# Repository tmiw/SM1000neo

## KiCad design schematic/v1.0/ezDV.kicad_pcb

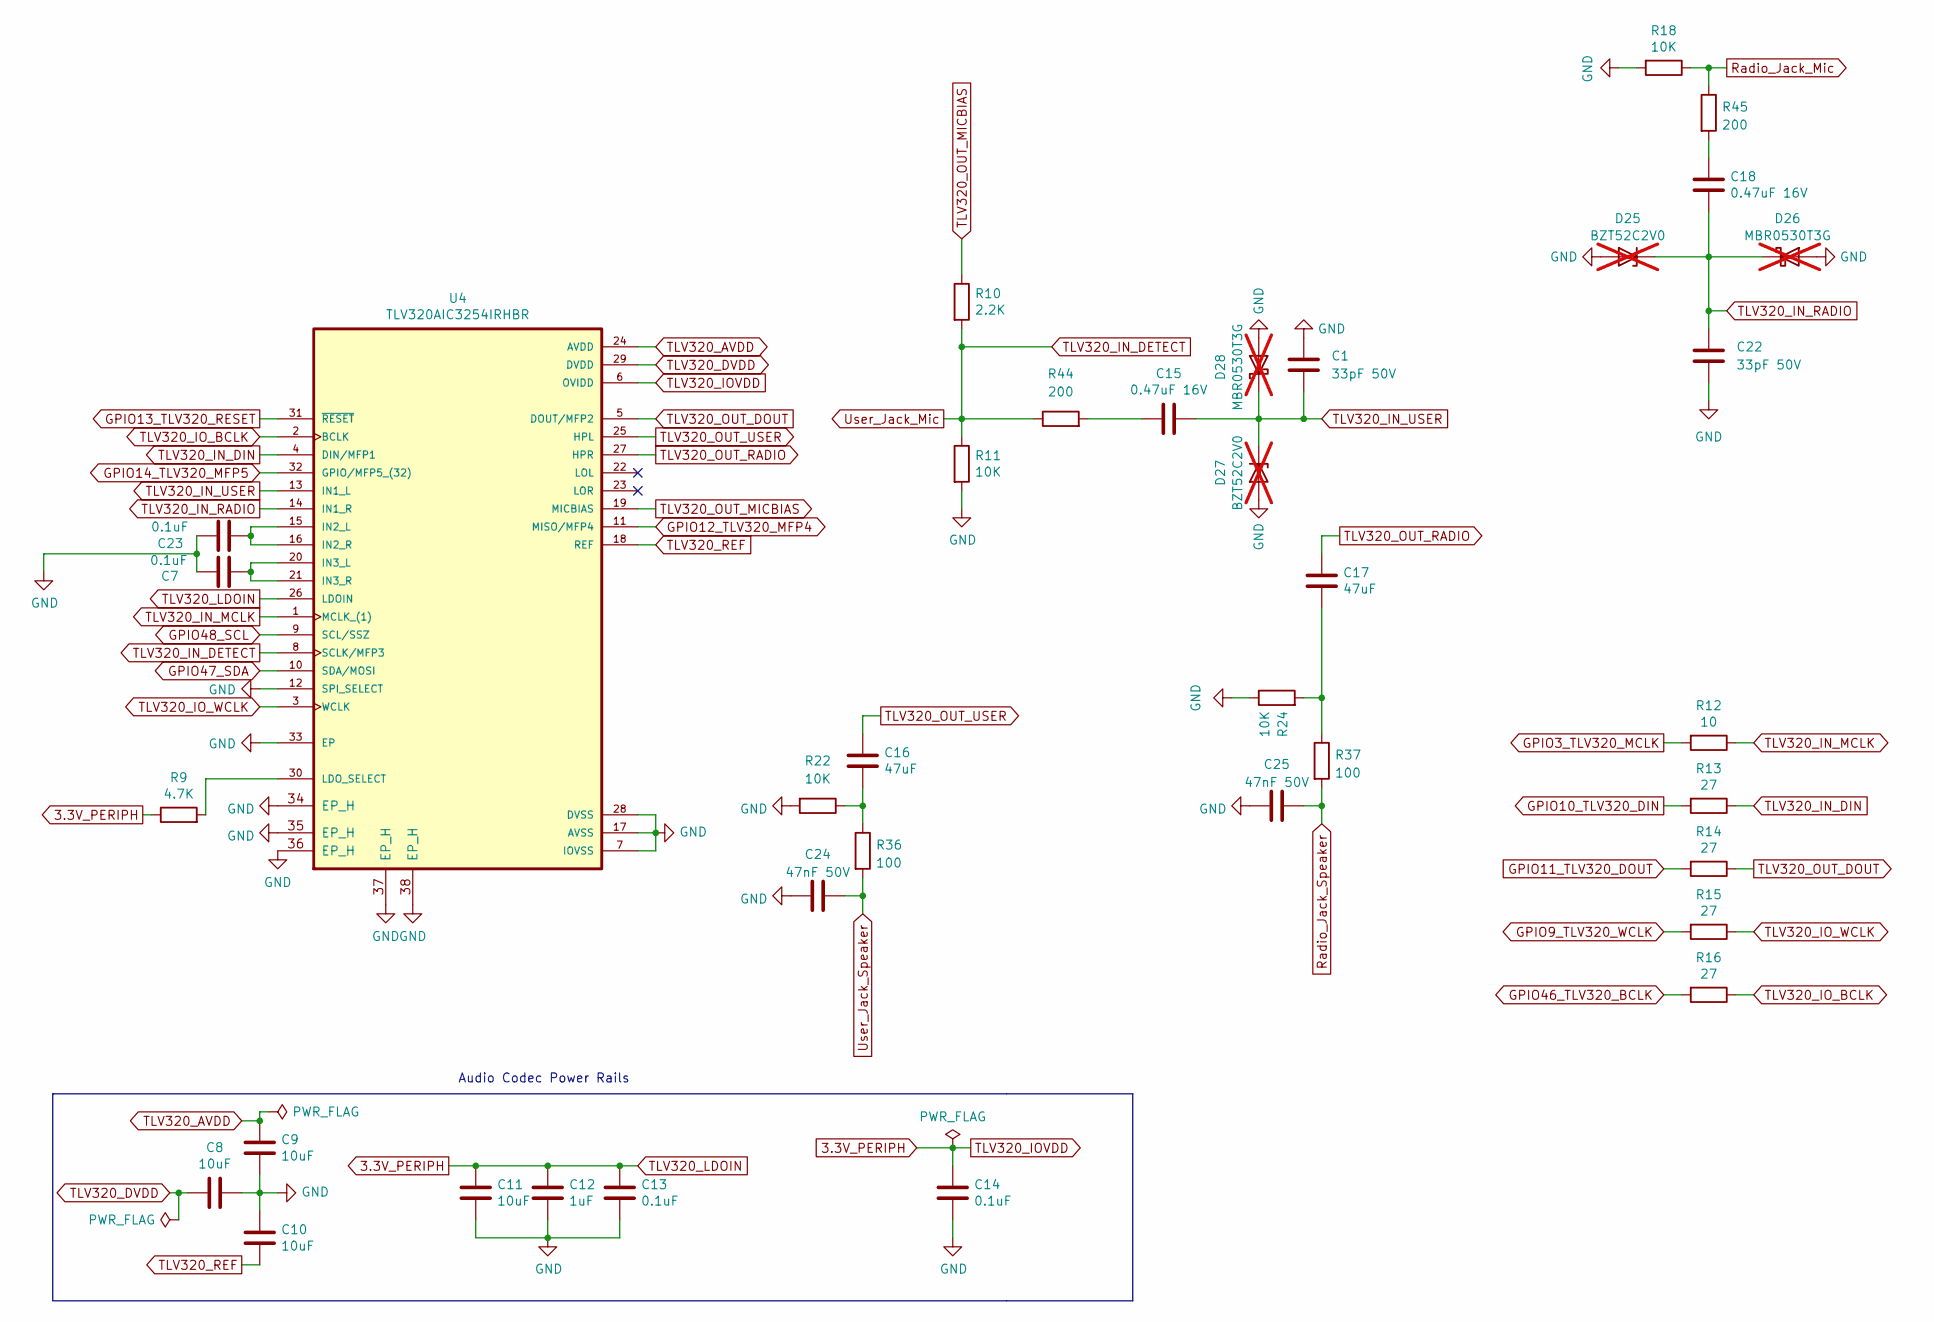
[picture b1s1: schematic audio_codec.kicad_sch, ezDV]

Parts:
C1, C22: 33pF 50V; C_0402_1005Metric; LCSC C1562
C7, C13, C14, C23: 0.1uF; C_0402_1005Metric; LCSC C1525
C8, C9, C10, C11: 10uF; C_0402_1005Metric; LCSC C15525
C12: 1uF; C_0402_1005Metric; LCSC C52923
C15, C18: 0.47uF 16V; C_0402_1005Metric; LCSC C575468
C16, C17: 47uF; C_0603_1608Metric; LCSC C140782
C24, C25: 47nF 50V; C_0402_1005Metric; LCSC C697422
D25: BZT52C2V0; D_SOD-123; LCSC_DNP C2891405; not fitted
D26: MBR0530T3G; D_SOD-123; LCSC_DNP C236079; not fitted
D27: BZT52C2V0; D_SOD-123; LCSC C2891405; not fitted
D28: MBR0530T3G; D_SOD-123; LCSC C236079; not fitted
R9: 4.7K; R_0402_1005Metric; LCSC C25900
R10: 2.2K; R_0402_1005Metric; LCSC C25879
R11, R18, R22, R24: 10K; R_0402_1005Metric; LCSC C25744
R12: 10; R_0402_1005Metric; LCSC C25077
R13, R14, R15, R16: 27; R_0402_1005Metric; LCSC C25100
R36, R37: 100; R_0402_1005Metric; LCSC C25076
R44, R45: 200; R_0402_1005Metric; LCSC C25087
U4: TLV320AIC3254IRHBR; IC_ADS125H01IRHBT; LCSC C9925

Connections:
3.3V_PERIPH: C11.1, C12.1, C13.1, C14.1, R9.1, U4.6 (OVIDD), U4.26 (LDOIN); also elsewhere on the board
GND: C1.1, C7.2, C8.1, C9.2, C10.1, C11.2, C12.2, C13.2, C14.2, C22.2, C23.2, C24.1, C25.1, D25.2 (A), D26.2 (A), D27.2 (A), D28.2 (A), R11.2, R18.2, R22.2, R24.1, U4.7 (IOVSS), U4.12 (SPI_SELECT), U4.17 (AVSS), U4.28 (DVSS), U4.33 (EP), U4.34 (EP_H), U4.35 (EP_H), U4.36 (EP_H), U4.37 (EP_H), U4.38 (EP_H); also elsewhere on the board
GPIO3_TLV320_MCLK: R12.2; also elsewhere on the board
GPIO9_TLV320_WCLK: R15.2; also elsewhere on the board
GPIO10_TLV320_DIN: R13.2; also elsewhere on the board
GPIO11_TLV320_DOUT: R14.2; also elsewhere on the board
GPIO12_TLV320_MFP4: U4.11 (MISO/MFP4); also elsewhere on the board
GPIO13_TLV320_RESET: U4.31 (~RESET); also elsewhere on the board
GPIO14_TLV320_MFP5: U4.32 (GPIO/MFP5_(32)); also elsewhere on the board
GPIO46_TLV320_BCLK: R16.2; also elsewhere on the board
GPIO47_SDA: U4.10 (SDA/MOSI); also elsewhere on the board
GPIO48_SCL: U4.9 (SCL/SSZ); also elsewhere on the board
unnamed: C15.1, R44.2
unnamed: C16.2, R22.1, R36.1
unnamed: C17.2, R24.2, R37.1
unnamed: C18.1, R45.2
unnamed: C7.1, U4.15 (IN2_L), U4.16 (IN2_R)
unnamed: C23.1, U4.20 (IN3_L), U4.21 (IN3_R)
unnamed: R9.2, U4.30 (LDO_SELECT)
Radio_Jack_Mic: R18.1, R45.1; also elsewhere on the board
Radio_Jack_Speaker: C25.2, R37.2; also elsewhere on the board
TLV320_AVDD: C9.1, U4.24 (AVDD)
TLV320_DVDD: C8.2, U4.29 (DVDD)
TLV320_IN_DETECT: R10.2, R11.1, R44.1, U4.8 (SCLK/MFP3); also elsewhere on the board
TLV320_IN_DIN: R13.1, U4.4 (DIN/MFP1)
TLV320_IN_MCLK: R12.1, U4.1 (MCLK_(1))
TLV320_IN_RADIO: C18.2, C22.1, D25.1 (K), D26.1 (K), U4.14 (IN1_R)
TLV320_IN_USER: C1.2, C15.2, D27.1 (K), D28.1 (K), U4.13 (IN1_L)
TLV320_IO_BCLK: R16.1, U4.2 (BCLK)
TLV320_IO_WCLK: R15.1, U4.3 (WCLK)
TLV320_OUT_DOUT: R14.1, U4.5 (DOUT/MFP2)
TLV320_OUT_MICBIAS: R10.1, U4.19 (MICBIAS)
TLV320_OUT_RADIO: C17.1, U4.27 (HPR)
TLV320_OUT_USER: C16.1, U4.25 (HPL)
TLV320_REF: C10.2, U4.18 (REF)
User_Jack_Speaker: C24.2, R36.2; also elsewhere on the board

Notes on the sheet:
Audio Codec Power Rails

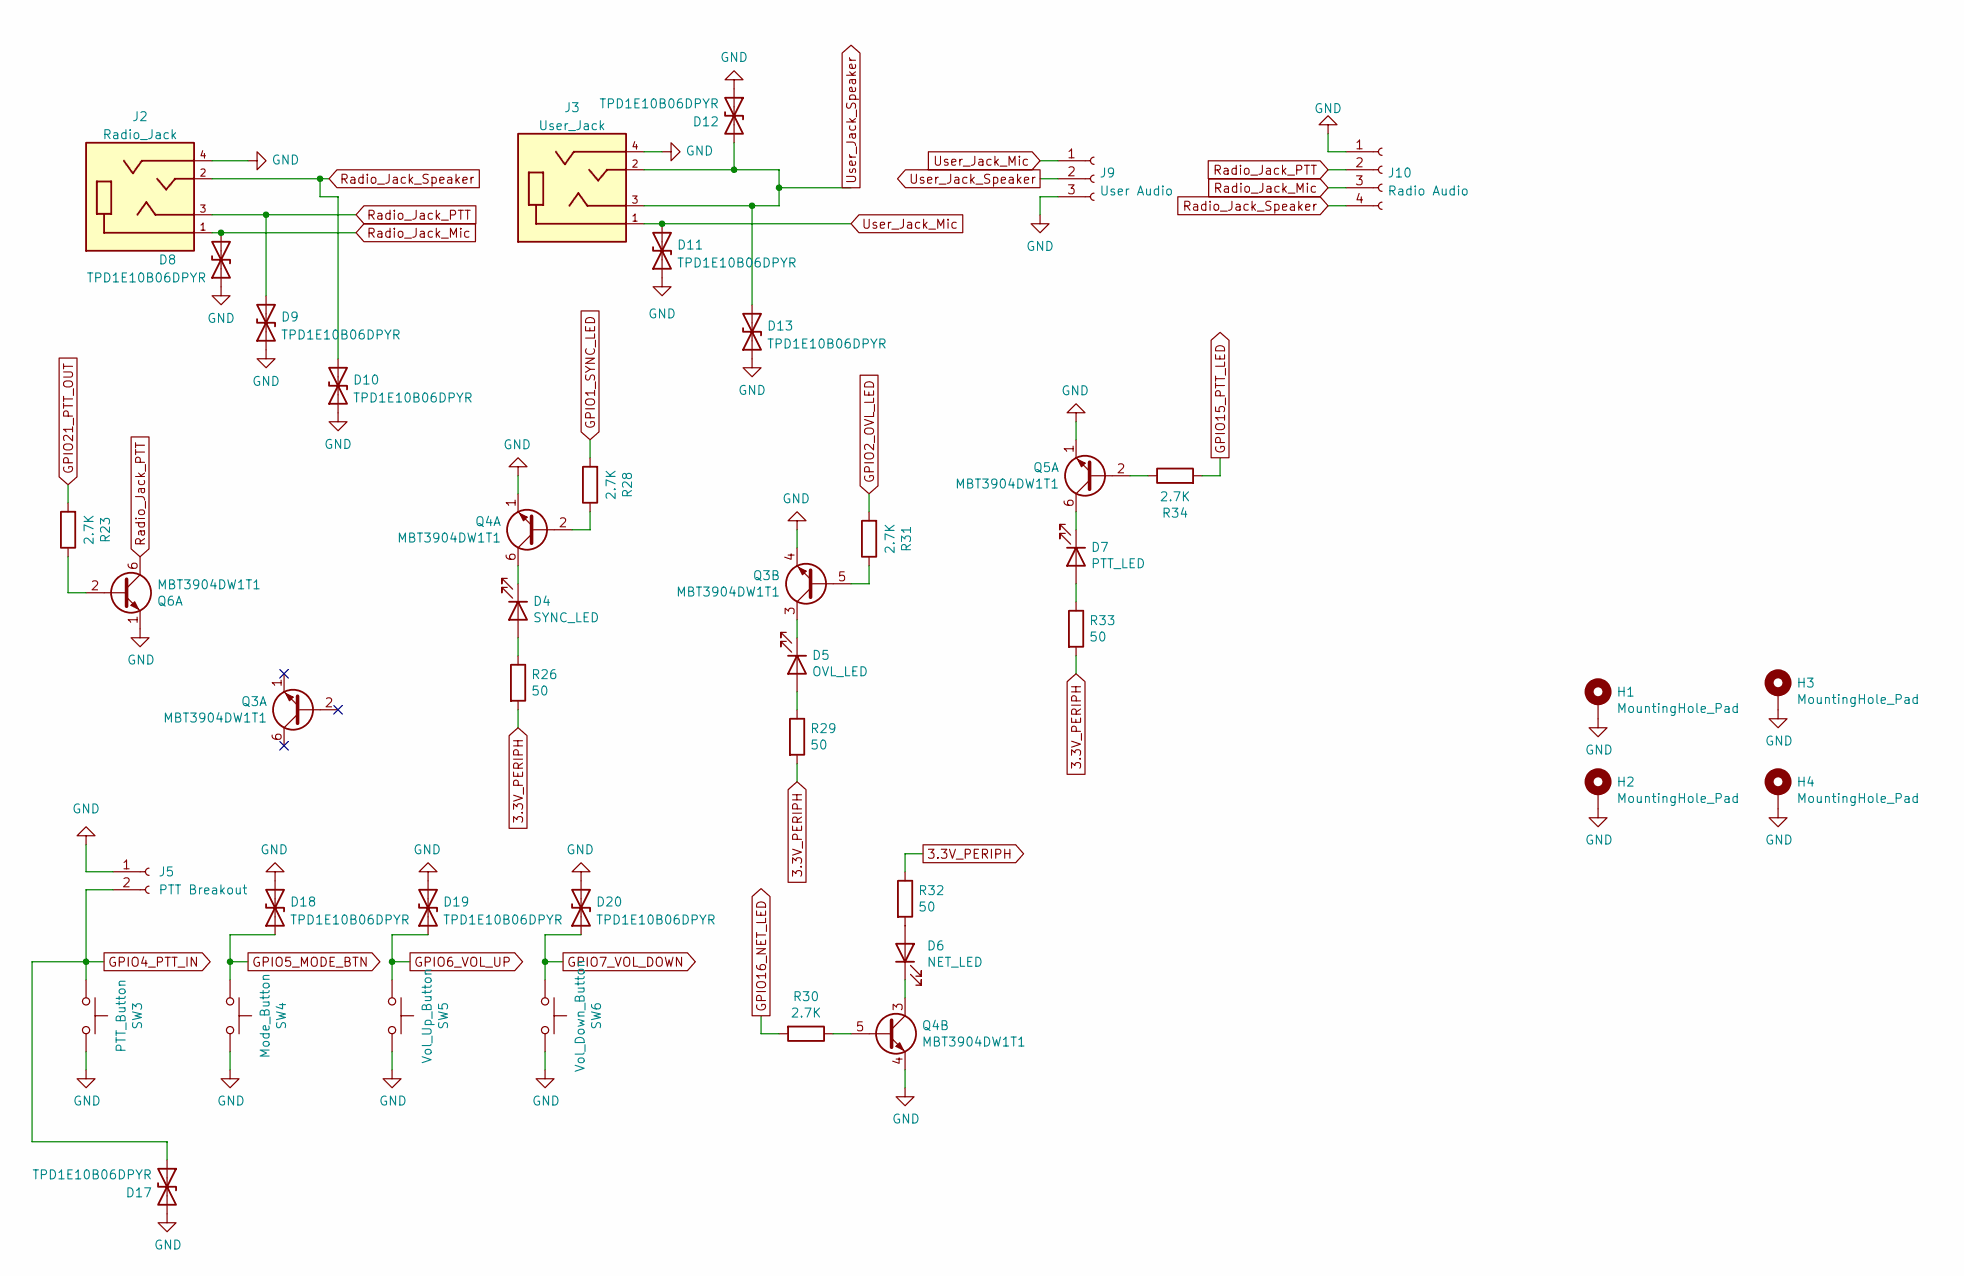
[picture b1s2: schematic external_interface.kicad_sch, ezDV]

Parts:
D4: SYNC_LED; D_0603_1608Metric; LCSC C965805
D5: OVL_LED; D_0603_1608Metric; LCSC C2286
D6: NET_LED; D_0603_1608Metric; LCSC C72041
D7: PTT_LED; D_0603_1608Metric; LCSC C2286
D8, D9, D10, D11, D12, D13, D17, D18, D19, D20: TPD1E10B06DPYR; DIO_TPD1E05U06DPYR; LCSC C48260
H1, H2, H3, H4: MountingHole_Pad; MountingHole_3.2mm_M3_Pad; JLCPCB_Basic N/A
J2: Radio_Jack; TRRS-PJ-320A; LCSC C2884926
J3: User_Jack; TRRS-PJ-320A; LCSC C2884926
J5: PTT Breakout; PinHeader_1x02_P2.54mm_Vertical; JLCPCB_Basic N/A
J9: User Audio; PinSocket_1x03_P2.54mm_Vertical; JLCPCB_Basic N/A
J10: Radio Audio; PinHeader_1x04_P2.54mm_Vertical; JLCPCB_Basic N/A
Q3, Q4, Q5, Q6: MBT3904DW1T1; SOT-363_SC-70-6; LCSC C110150
R23, R28, R30, R31, R34: 2.7K; R_0603_1608Metric; LCSC C13167
R26, R29, R32, R33: 50; R_0603_1608Metric; LCSC C22808
SW3: PTT_Button; SW_PUSH_6mm_H4.3mm; LCSC C2837517
SW4: Mode_Button; SW_PUSH_6mm_H4.3mm; LCSC C2837517
SW5: Vol_Up_Button; SW_PUSH_6mm_H4.3mm; LCSC C2837517
SW6: Vol_Down_Button; SW_PUSH_6mm_H4.3mm; LCSC C2837517

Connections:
3.3V_PERIPH: R26.2, R29.2, R32.1, R33.2; also elsewhere on the board
GND: D8.1 (A1), D9.1 (A1), D10.1 (A1), D11.1 (A1), D12.1 (A1), D13.1 (A1), D17.2 (A2), D18.2 (A2), D19.2 (A2), D20.2 (A2), H1.1, H2.1, H3.1, H4.1, J2.4, J3.4, J5.1, J9.3, J10.1, Q3.4 (E2), Q4.1 (E1), Q4.4 (E2), Q5.1 (E1), Q6.1 (E1), SW3.2, SW4.2, SW5.2, SW6.2; also elsewhere on the board
GPIO1_SYNC_LED: R28.2; also elsewhere on the board
GPIO2_OVL_LED: R31.2; also elsewhere on the board
GPIO4_PTT_IN: D17.1 (A1), J5.2, SW3.1; also elsewhere on the board
GPIO5_MODE_BTN: D18.1 (A1), SW4.1; also elsewhere on the board
GPIO6_VOL_UP: D19.1 (A1), SW5.1; also elsewhere on the board
GPIO7_VOL_DOWN: D20.1 (A1), SW6.1; also elsewhere on the board
GPIO15_PTT_LED: R34.2; also elsewhere on the board
GPIO16_NET_LED: R30.2; also elsewhere on the board
GPIO21_PTT_OUT: R23.2; also elsewhere on the board
unnamed: D4.2 (A), R26.1
unnamed: D4.1 (K), Q4.6 (C1)
unnamed: D5.2 (A), R29.1
unnamed: D5.1 (K), Q3.3 (C2)
unnamed: D6.2 (A), R32.2
unnamed: D6.1 (K), Q4.3 (C2)
unnamed: D7.2 (A), R33.1
unnamed: D7.1 (K), Q5.6 (C1)
unnamed: Q3.5 (B2), R31.1
unnamed: Q4.2 (B1), R28.1
unnamed: Q4.5 (B2), R30.1
unnamed: Q5.2 (B1), R34.1
unnamed: Q6.2 (B1), R23.1
Radio_Jack_Mic: D8.2 (A2), J2.1, J10.3; also elsewhere on the board
Radio_Jack_PTT: D9.2 (A2), J2.3, J10.2, Q6.6 (C1)
Radio_Jack_Speaker: D10.2 (A2), J2.2, J10.4; also elsewhere on the board
TLV320_IN_DETECT: D11.2 (A2), J3.1, J9.1; also elsewhere on the board
User_Jack_Speaker: D12.2 (A2), D13.2 (A2), J3.2, J3.3, J9.2; also elsewhere on the board

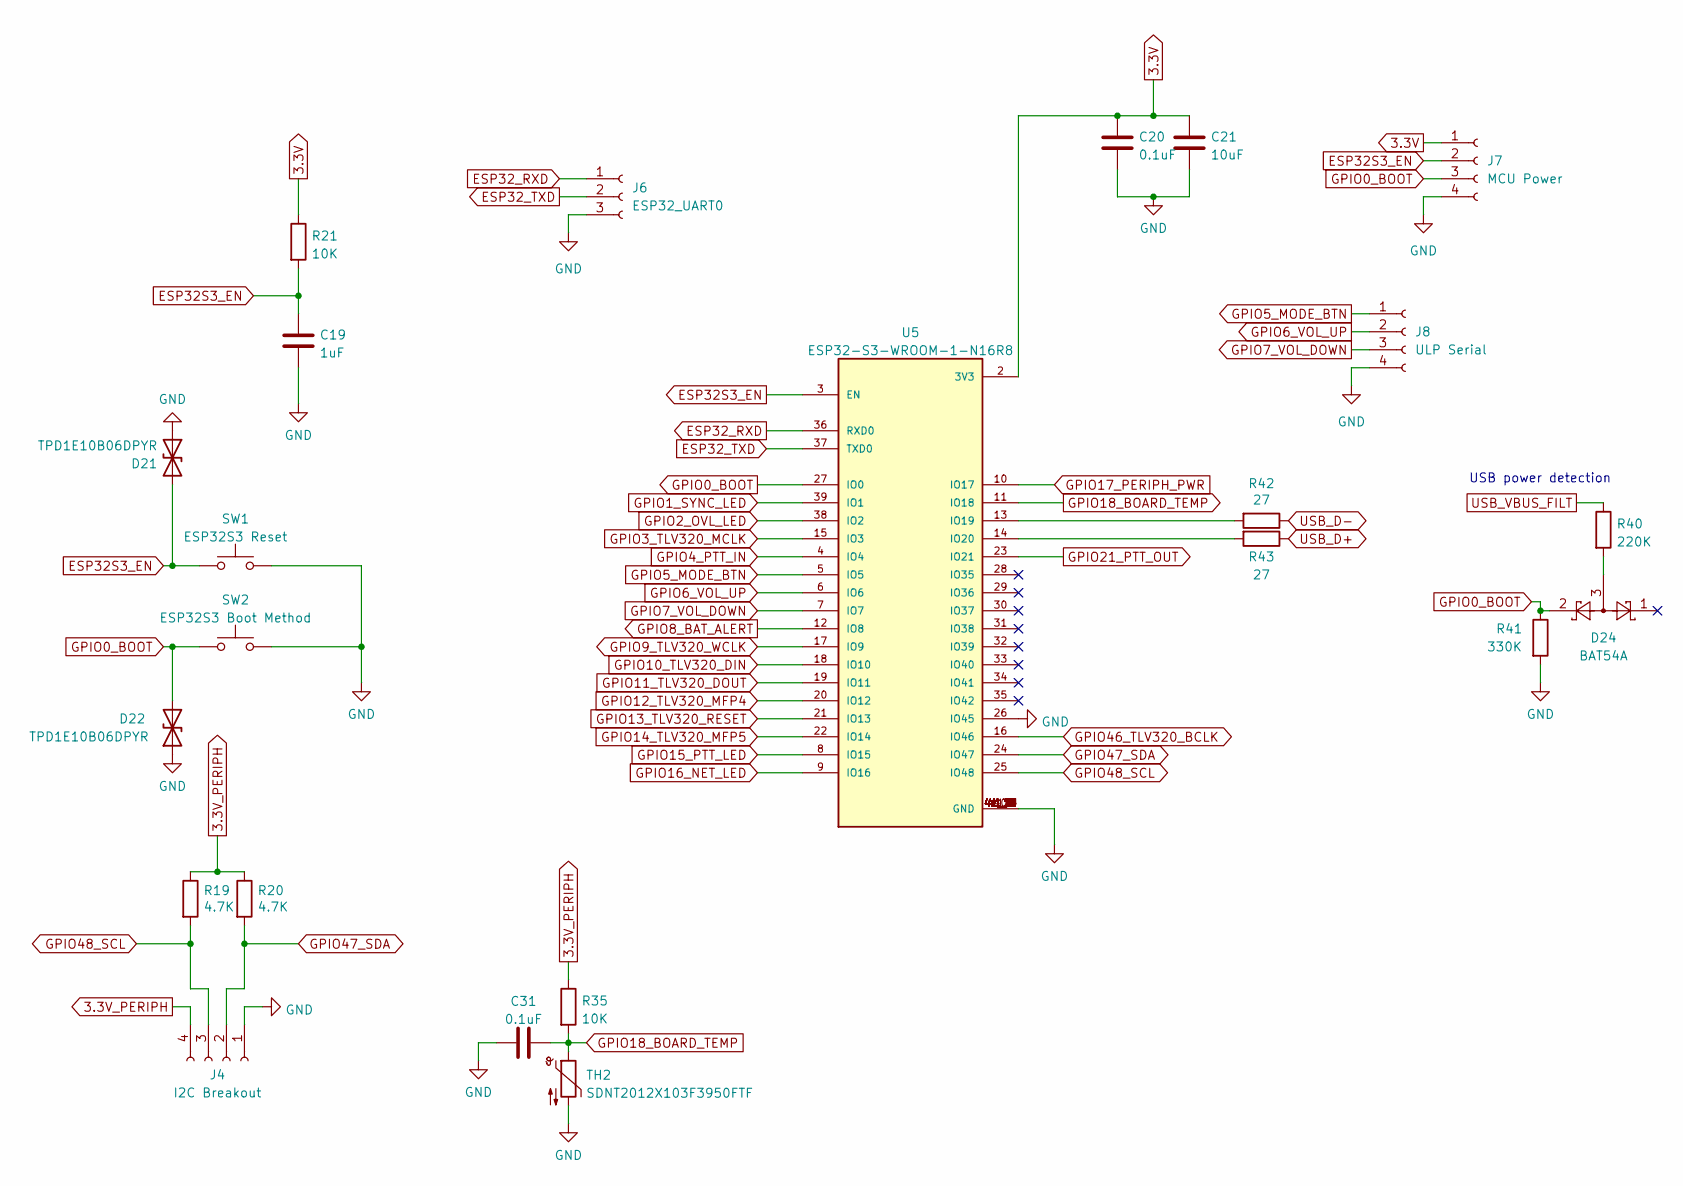
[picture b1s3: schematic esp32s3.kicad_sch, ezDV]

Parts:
C19: 1uF; C_0402_1005Metric; LCSC C52923
C20, C31: 0.1uF; C_0402_1005Metric; LCSC C1525
C21: 10uF; C_0402_1005Metric; LCSC C15525
D21, D22: TPD1E10B06DPYR; DIO_TPD1E05U06DPYR; LCSC C48260
D24: BAT54A; SOT-23; LCSC C134401
J4: I2C Breakout; PinHeader_2x02_P2.54mm_Vertical; JLCPCB_Basic N/A
J6: ESP32_UART0; PinHeader_1x03_P2.54mm_Vertical; JLCPCB_Basic N/A
J7: MCU Power; PinHeader_1x04_P2.54mm_Vertical; JLCPCB_Basic N/A
J8: ULP Serial; PinHeader_2x02_P2.54mm_Vertical; JLCPCB_Basic N/A
R19, R20: 4.7K; R_0603_1608Metric; LCSC C23162
R21, R35: 10K; R_0402_1005Metric; LCSC C25744
R40: 220K; R_0402_1005Metric; LCSC C25767
R41: 330K; R_0402_1005Metric; LCSC C25778
R42, R43: 27; R_0402_1005Metric; LCSC C25100
SW1: ESP32S3 Reset; SW_PUSH_6mm_H4.3mm; LCSC C2837514
SW2: ESP32S3 Boot Method; SW_PUSH_6mm_H4.3mm; LCSC C2837514
TH2: SDNT2012X103F3950FTF; R_0805_2012Metric; LCSC C95968
U5: ESP32-S3-WROOM-1-N16R8; XCVR_ESP32S3WROOM1N8R8; LCSC C2913202

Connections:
3.3V: C20.1, C21.1, J7.1, R21.1, U5.2 (3V3); also elsewhere on the board
3.3V_PERIPH: J4.4, R19.1, R20.1, R35.1; also elsewhere on the board
ESP32S3_EN: C19.1, D21.2 (A2), J7.2, R21.2, SW1.1, U5.3 (EN)
ESP32_RXD: J6.1, U5.36 (RXD0)
ESP32_TXD: J6.2, U5.37 (TXD0)
GND: C19.2, C20.2, C21.2, C31.1, D21.1 (A1), D22.1 (A1), J4.1, J6.3, J7.4, J8.4, R41.2, SW1.2, SW2.2, TH2.2, U5.1 (GND), U5.26 (IO45), U5.40 (GND), U5.41_1 (GND), U5.41_2 (GND), U5.41_3 (GND), U5.41_4 (GND), U5.41_5 (GND), U5.41_6 (GND), U5.41_7 (GND), U5.41_8 (GND), U5.41_9 (GND), U5.41_10 (GND), U5.41_11 (GND), U5.41_12 (GND), U5.41_13 (GND), U5.41_14 (GND), U5.41_15 (GND), U5.41_16 (GND), U5.41_17 (GND), U5.41_18 (GND), U5.41_19 (GND), U5.41_20 (GND), U5.41_21 (GND); also elsewhere on the board
GPIO0_BOOT: D22.2 (A2), D24.2, J7.3, R41.1, SW2.1, U5.27 (IO0)
GPIO1_SYNC_LED: U5.39 (IO1); also elsewhere on the board
GPIO2_OVL_LED: U5.38 (IO2); also elsewhere on the board
GPIO3_TLV320_MCLK: U5.15 (IO3); also elsewhere on the board
GPIO4_PTT_IN: U5.4 (IO4); also elsewhere on the board
GPIO5_MODE_BTN: J8.1, U5.5 (IO5); also elsewhere on the board
GPIO6_VOL_UP: J8.2, U5.6 (IO6); also elsewhere on the board
GPIO7_VOL_DOWN: J8.3, U5.7 (IO7); also elsewhere on the board
GPIO8_BAT_ALERT: U5.12 (IO8); also elsewhere on the board
GPIO9_TLV320_WCLK: U5.17 (IO9); also elsewhere on the board
GPIO10_TLV320_DIN: U5.18 (IO10); also elsewhere on the board
GPIO11_TLV320_DOUT: U5.19 (IO11); also elsewhere on the board
GPIO12_TLV320_MFP4: U5.20 (IO12); also elsewhere on the board
GPIO13_TLV320_RESET: U5.21 (IO13); also elsewhere on the board
GPIO14_TLV320_MFP5: U5.22 (IO14); also elsewhere on the board
GPIO15_PTT_LED: U5.8 (IO15); also elsewhere on the board
GPIO16_NET_LED: U5.9 (IO16); also elsewhere on the board
GPIO17_PERIPH_PWR: U5.10 (IO17); also elsewhere on the board
GPIO18_BOARD_TEMP: C31.2, R35.2, TH2.1, U5.11 (IO18)
GPIO21_PTT_OUT: U5.23 (IO21); also elsewhere on the board
GPIO46_TLV320_BCLK: U5.16 (IO46); also elsewhere on the board
GPIO47_SDA: J4.2, R20.2, U5.24 (IO47); also elsewhere on the board
GPIO48_SCL: J4.3, R19.2, U5.25 (IO48); also elsewhere on the board
unnamed: D24.3, R40.2
unnamed: R42.2, U5.13 (IO19)
unnamed: R43.2, U5.14 (IO20)
USB_D+: R43.1; also elsewhere on the board
USB_D-: R42.1; also elsewhere on the board
USB_VBUS_FILT: R40.1; also elsewhere on the board

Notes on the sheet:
USB power detection

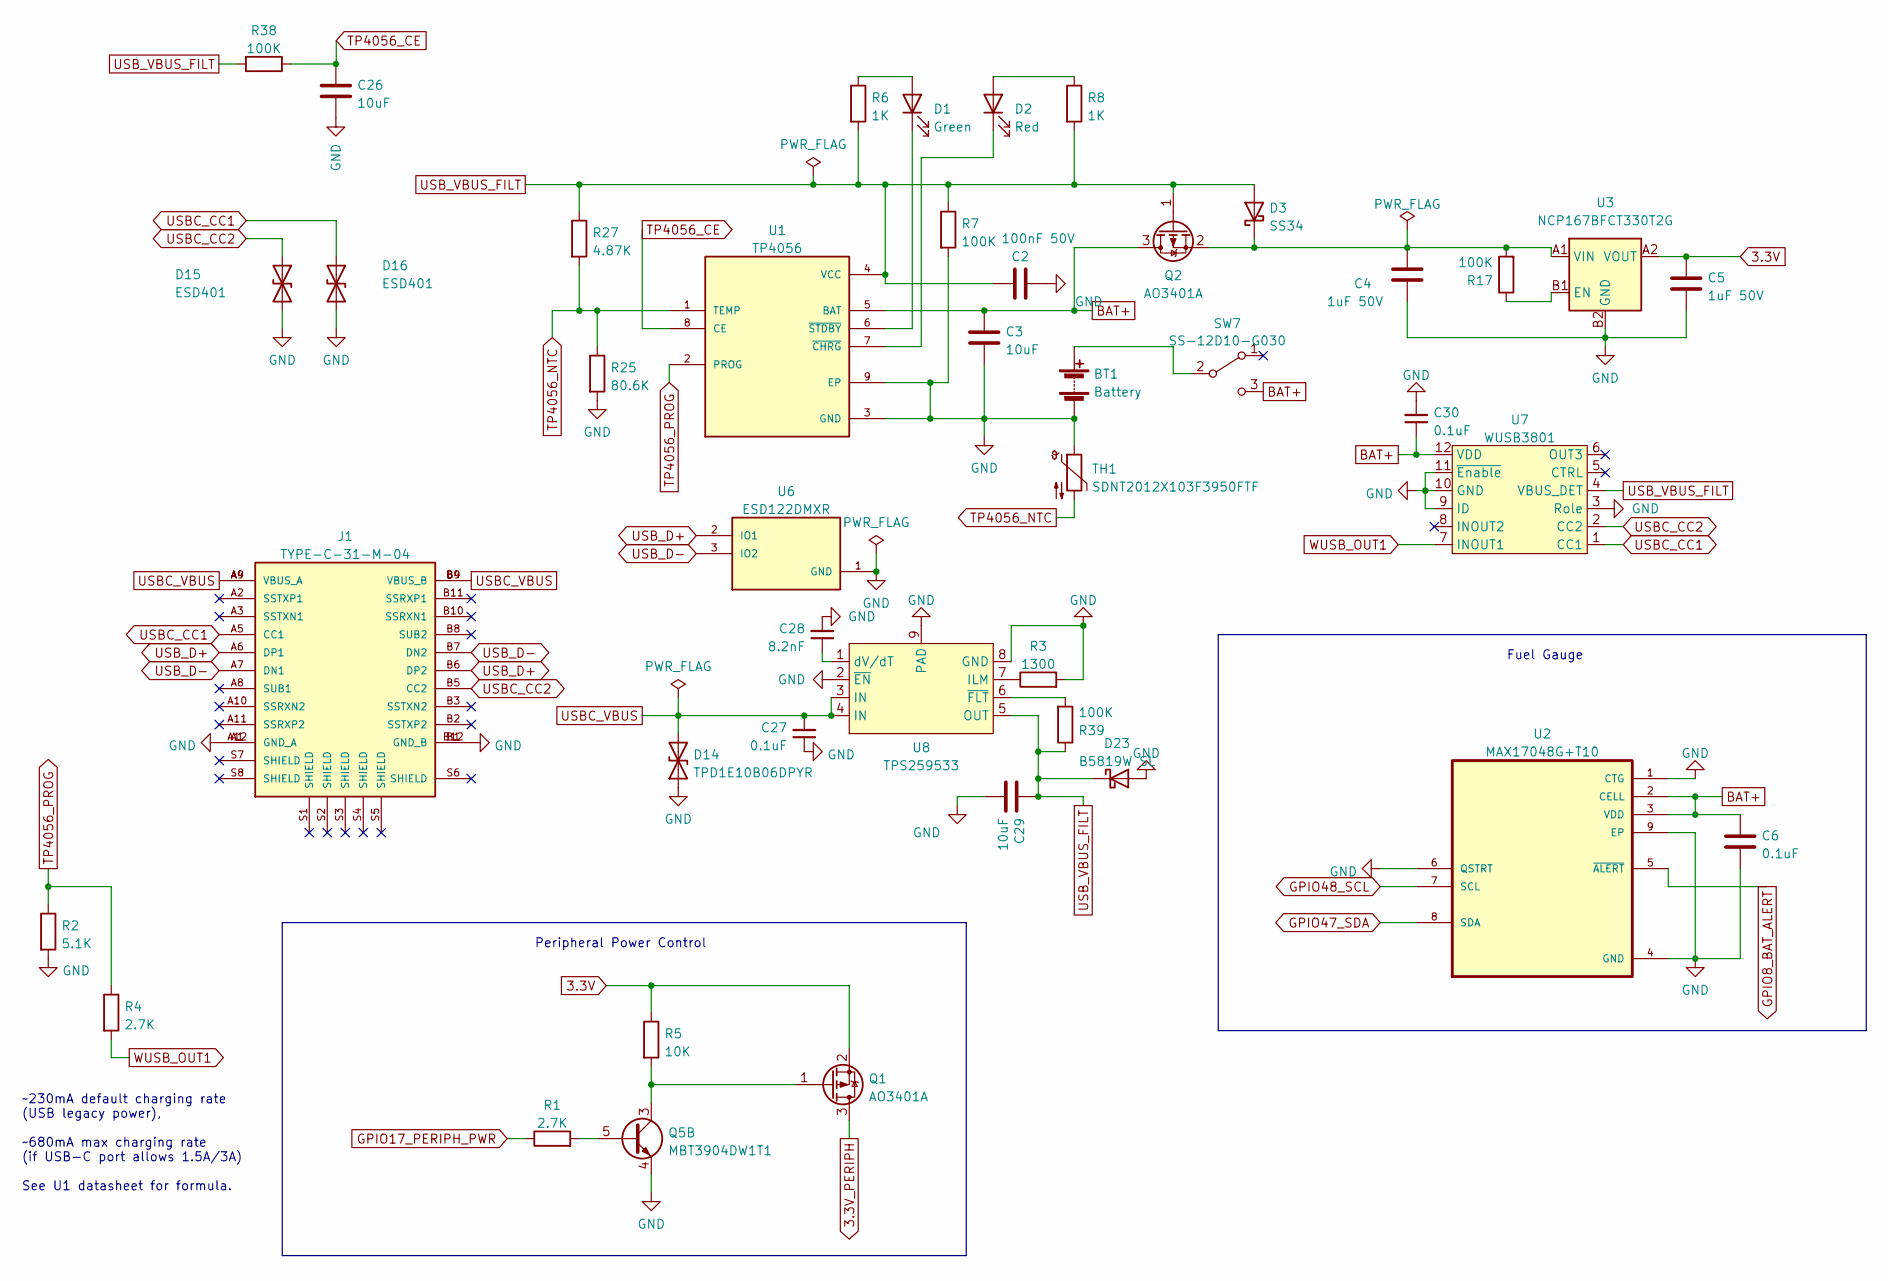
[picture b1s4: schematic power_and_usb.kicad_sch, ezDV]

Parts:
BT1: Battery; JST_PH_B2B-PH-K_1x02_P2.00mm_Vertical; LCSC C2319
C2: 100nF 50V; C_0402_1005Metric; LCSC C307331
C3, C26, C29: 10uF; C_0603_1608Metric; LCSC C96446
C4, C5: 1uF 50V; C_0805_2012Metric; LCSC C28323
C6, C27, C30: 0.1uF; C_0402_1005Metric; LCSC C1525
C28: 8.2nF; C_0402_1005Metric; LCSC C309459
D1: Green; D_0603_1608Metric; LCSC C72043
D2: Red; D_0603_1608Metric; LCSC C2286
D3: SS34; D_SMA; LCSC C8678
D14: TPD1E10B06DPYR; DIO_TPD1E05U06DPYR; LCSC C48260
D15, D16: ESD401; DIO_TPD1E05U06DPYR; LCSC C1974752
D23: B5819W SL; D_SOD-123; LCSC C8598
J1: TYPE-C-31-M-04; HRO_TYPE-C-31-M-04; PARTREV A; LCSC C129018
Q1, Q2: AO3401A; SOT-23; LCSC C15127
Q5: MBT3904DW1T1; SOT-363_SC-70-6; LCSC C110150
R1, R4: 2.7K; R_0603_1608Metric; LCSC C13167
R2: 5.1K; R_0402_1005Metric; LCSC C25905
R3: 1300; R_0402_1005Metric; LCSC C2974006
R5: 10K; R_0402_1005Metric; LCSC C25744
R6, R8: 1K; R_0402_1005Metric; LCSC C11702
R7, R17, R38, R39: 100K; R_0402_1005Metric; LCSC C25741
R25: 80.6K; R_0603_1608Metric; LCSC C103827
R27: 4.87K; R_0805_2012Metric; LCSC C104361
SW7: SS-12D10-G030; SS-12D10L3; LCSC C5155547
TH1: SDNT2012X103F3950FTF; R_0805_2012Metric; LCSC C95968
U1: TP4056; SOP127P600X175-9N; LCSC C16581
U2: MAX17048G+T10; SON50P200X200X80-9N; LCSC C2682616
U3: NCP167BFCT330T2G; BGA4N35P2X2_64X64X33N; LCSC C603663
U6: ESD122DMXR; IC_ESD122DMXR; PARTREV A; LCSC C544474
U7: WUSB3801; QFN1616-12L; LCSC C2931342
U8: TPS259533; WSON-8-1EP_2x2mm_P0.5mm_EP0.9x1.6mm_ThermalVias; LCSC C2155777

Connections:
3.3V: C5.1, Q1.2 (S), R5.1, U3.A2 (VOUT); also elsewhere on the board
3.3V_PERIPH: Q1.3 (D); also elsewhere on the board
BAT+: C3.1, C6.1, C30.1, Q2.3 (D), SW7.3 (C), U1.5 (BAT), U2.2 (CELL), U2.3 (VDD), U7.12 (VDD)
GND: BT1.2 (-), C2.1, C3.2, C4.2, C5.2, C6.2, C26.1, C27.1, C28.2, C29.2, C30.2, D14.1 (A1), D15.2 (A2), D16.2 (A2), D23.2 (A), J1.A1 (GND_A), J1.A12 (GND_A), J1.B1 (GND_B), J1.B12 (GND_B), Q5.4 (E2), R2.2, R3.2, R7.2, R25.2, TH1.1, U1.3 (GND), U1.9 (EP), U2.1 (CTG), U2.4 (GND), U2.6 (QSTRT), U2.9 (EP), U3.B2 (GND), U6.1 (GND), U7.3 (Role), U7.9 (ID), U7.10 (GND), U7.11 (~Enable), U8.2 (~EN), U8.8 (GND), U8.9 (PAD); also elsewhere on the board
GPIO8_BAT_ALERT: U2.5 (~ALERT); also elsewhere on the board
GPIO17_PERIPH_PWR: R1.1; also elsewhere on the board
GPIO47_SDA: U2.8 (SDA); also elsewhere on the board
GPIO48_SCL: U2.7 (SCL); also elsewhere on the board
unnamed: BT1.1 (+), SW7.2 (B)
unnamed: D1.2 (A), R6.1
unnamed: D1.1 (K), U1.6 (~STDBY)
unnamed: D2.2 (A), R8.1
unnamed: D2.1 (K), U1.7 (~CHRG)
unnamed: C4.1, D3.1 (K), Q2.2 (S), R17.2, U3.A1 (VIN)
unnamed: Q1.1 (G), Q5.3 (C2), R5.2
unnamed: Q5.5 (B2), R1.2
unnamed: R17.1, U3.B1 (EN)
unnamed: R3.1, U8.7 (ILM)
unnamed: C28.1, U8.1 (dV/dT)
unnamed: R39.2, U8.6 (~FLT)
TP4056_CE: C26.2, R38.1, U1.8 (CE)
TP4056_NTC: R25.1, R27.2, TH1.2, U1.1 (TEMP)
TP4056_PROG: R2.1, R4.1, U1.2 (PROG)
USBC_CC1: D16.1 (A1), J1.A5 (CC1), U7.1 (CC1)
USBC_CC2: D15.1 (A1), J1.B5 (CC2), U7.2 (CC2)
USBC_VBUS: C27.2, D14.2 (A2), J1.A4 (VBUS_A), J1.A9 (VBUS_A), J1.B4 (VBUS_B), J1.B9 (VBUS_B), U8.3 (IN), U8.4 (IN)
USB_D+: J1.A6 (DP1), J1.B6 (DP2), U6.2 (IO1); also elsewhere on the board
USB_D-: J1.A7 (DN1), J1.B7 (DN2), U6.3 (IO2); also elsewhere on the board
USB_VBUS_FILT: C2.2, C29.1, D3.2 (A), D23.1 (K), Q2.1 (G), R6.2, R7.1, R8.2, R27.1, R38.2, R39.1, U1.4 (VCC), U7.4 (VBUS_DET), U8.5 (OUT); also elsewhere on the board
WUSB_OUT1: R4.2, U7.7 (INOUT1)

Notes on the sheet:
Fuel Gauge
Peripheral Power Control
~230mA default charging rate (USB legacy power), ~680mA max charging rate (if USB-C port allows 1.5A/3A) See U1 datasheet for formula.

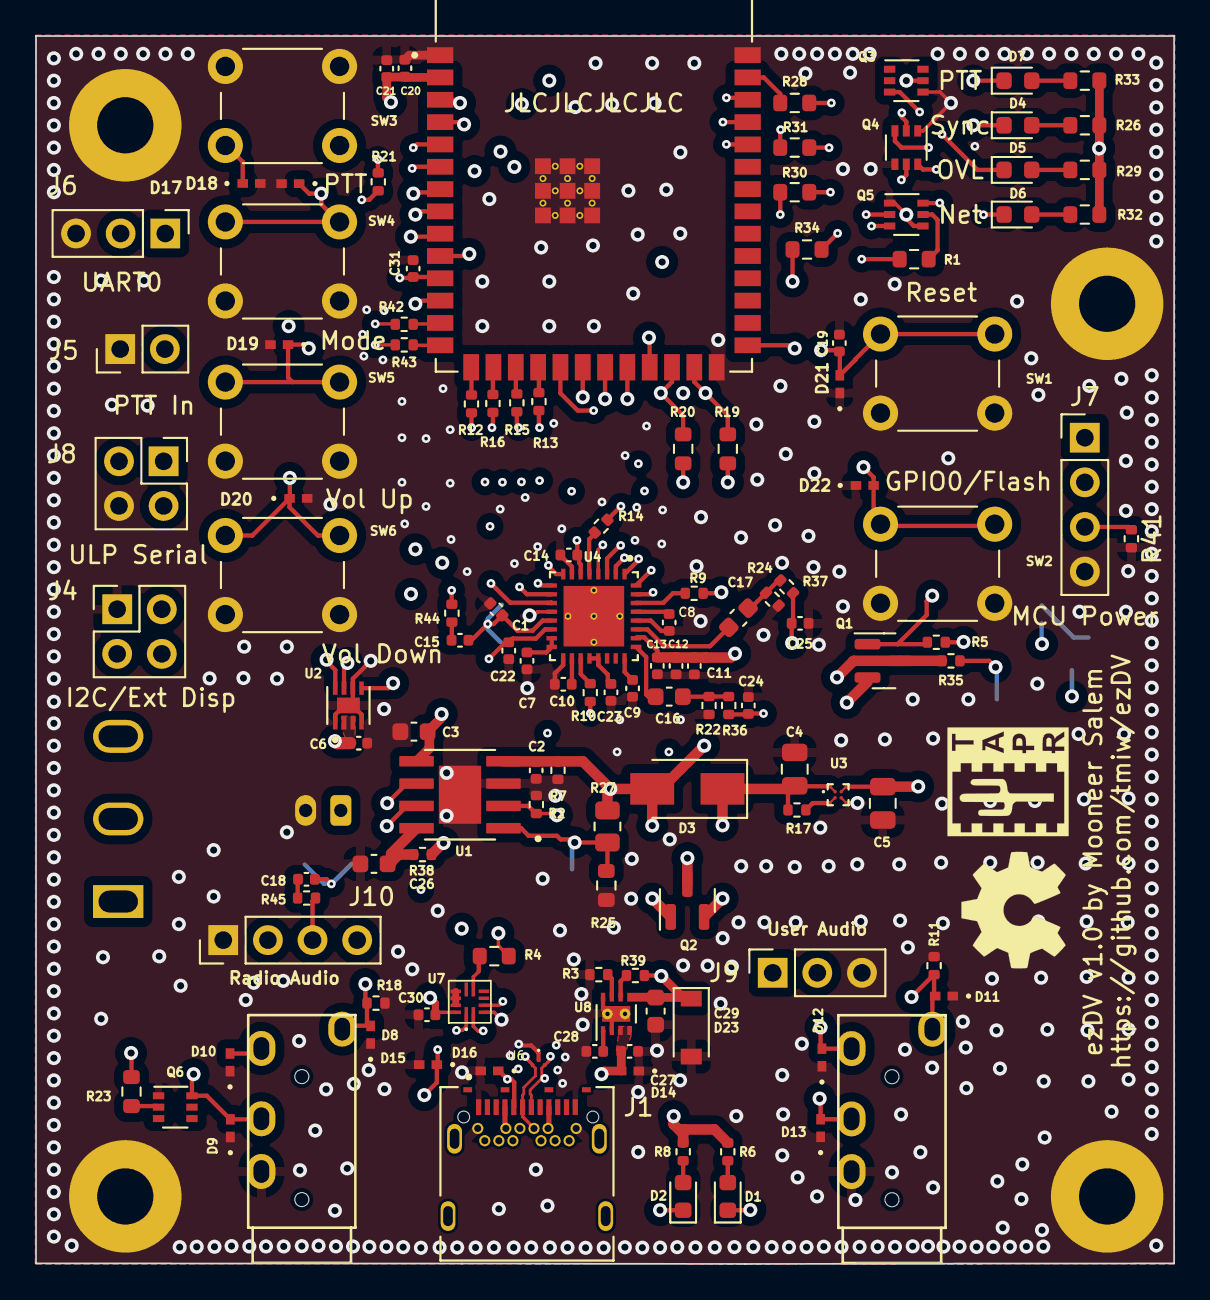
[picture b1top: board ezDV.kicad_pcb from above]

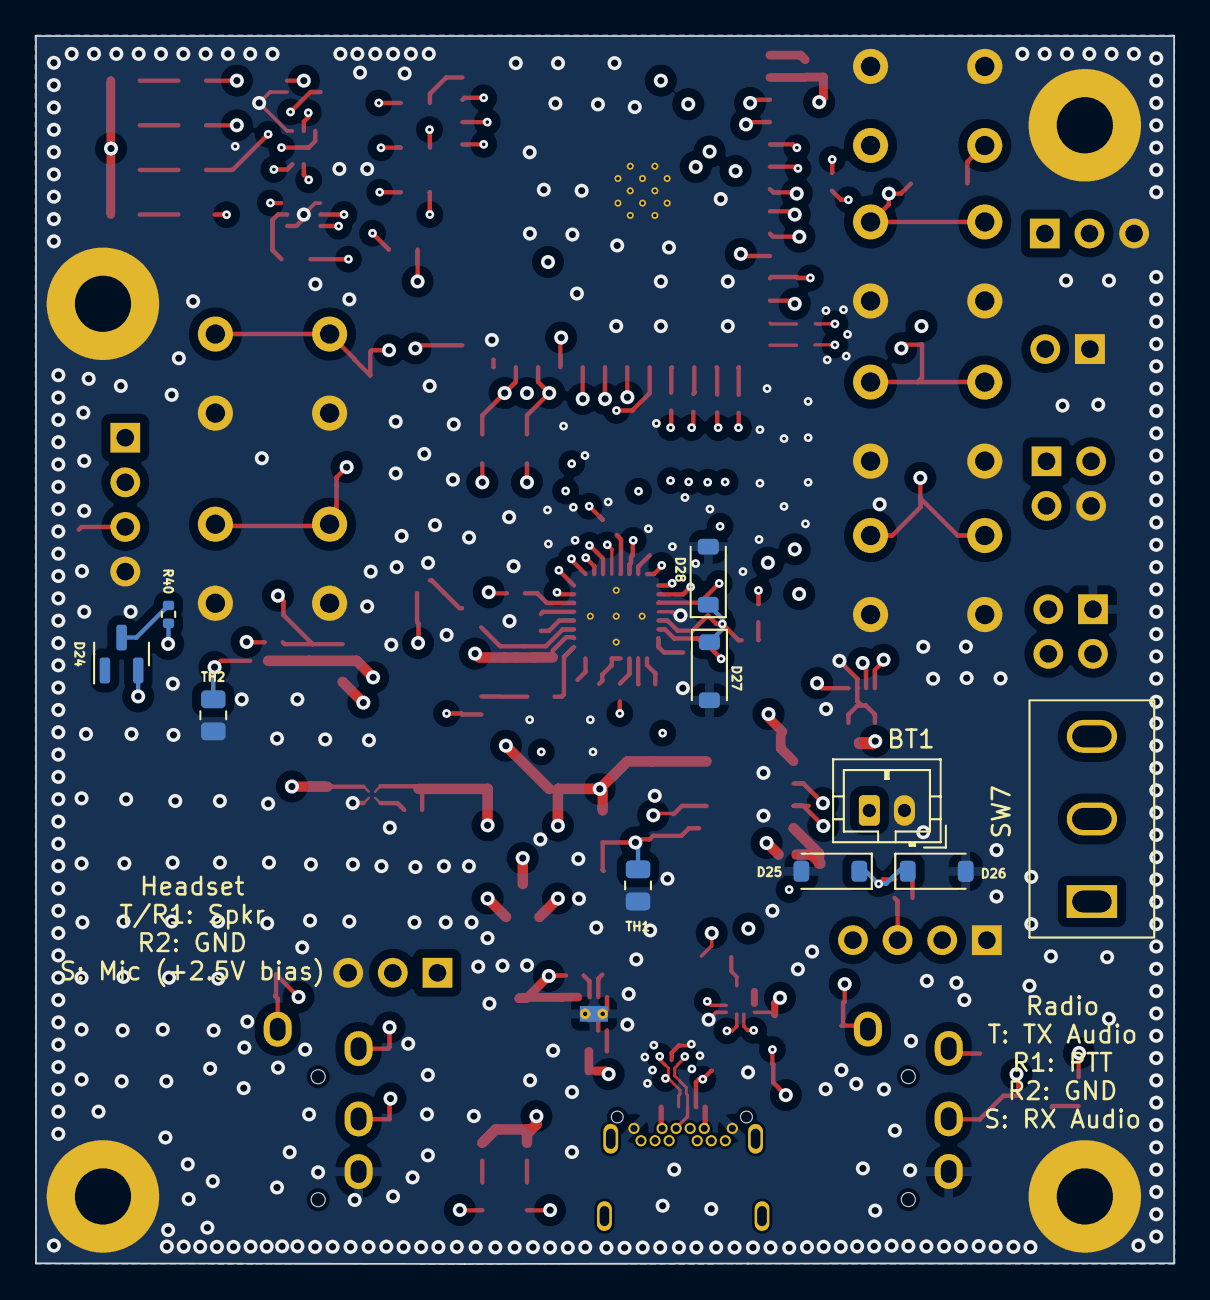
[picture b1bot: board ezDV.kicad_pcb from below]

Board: 6 copper layers, 64.8 x 69.9 mm, 142 parts (10 on the bottom side), 93 nets.

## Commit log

2024-10-30 Integrate v1.0 KiCad files.
